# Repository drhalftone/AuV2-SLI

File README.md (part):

# AuV2-SLI — an FPGA structured-light scanner with the camera inside it

A **BYOP (Bring Your Own Projector) machine-vision camera**: an Alchitry **Pt V2**
(Xilinx Artix-7 **XC7A100T-2**) sits inline on HDMI between a PC and a projector, and carries
an **ON Semi PYTHON 1300** global-shutter sensor on a stacked daughter board. One bitstream
generates the structured-light patterns, drives the projector, triggers the sensor at a
commanded delay from the projected vsync, and streams 10-bit frames to the host over an
**Alchitry Ft+** (FT601Q) USB 3.0 link.

The FPGA can:

- **Pass HDMI through** from a PC to the projector, triggering the camera on each new frame.
- **Replace the video with on-board SLI fringes** — resolution-adaptive, generated on the fly.
- **Run fully offline, with no HDMI source at all** — it reads the projector's EDID and drives
  it at a mode the projector actually advertises, up to **1280×1024@60** or **800×600@120**.
- **Genlock capture to projection** — camera triggers are issued a programmable delay after the
  projected vsync, and **stack**, so patterns advance at the full HDMI frame rate instead of at
  (exposure + delay).
- **Stream to the PC over USB 3** — 1280×1024 × 10 bit, byte-exact, up to 120 fps sustained.

> The HDMI datapath is adapted from [hamsternz/Artix-7-HDMI-processing](https://github.com/hamsternz/Artix-7-HDMI-processing) (MIT).
> Original SLI design by Qishi Hu. This fork adds the EDID-driven offline output, the adaptive
> pass-through clocking, the CEA-aware EDID merge, the PYTHON 1300 receive chain, the Ft+ USB 3
> image path, and genlock.

---

## 0. Quick orientation — what this repo is, on one screen

| | |
|---|---|
| **FPGA** | Alchitry **Pt V2**, `xc7a100tfgg484-2` (the original Au V2 / XC7A35T build still exists — `build.tcl`) |
| **Top level** | `sources_1/imports/RTL/Au2_SLI.vhd` (VHDL, instantiating the Verilog subsystems) |
| **Current build** | `build_merged.tcl` → `build_merged/Au2_SLI_merged.{bit,bin}` — HDMI/SLI **+** camera **+** Ft+ |
| **Constraints** | `constrs_1/imports/RTL/Au2_pt.xdc` + `pt_ftplus_merged.xdc` |
| **Camera** | ON Semi **PYTHON 1300**, now the **colour** `NOIP1SE1300A` (Bayer) in an Andon socket — the mono `NOIP1SN1300A-QTI` before it. 1280×1024, global shutter, 4-lane LVDS @ 720 Mbps |
| **Camera board** | `LauPythonCamera_Pt_Stack/` — the KiCad board **and** its Verilog (`ddr/`) |
| **Image path** | Alchitry **Ft+** (FT601Q) USB 3.0 — ~325 MB/s measured, 132 fps at 10-bit |
| **Control path** | the same Ft+ (opcode-0 tunnel), **and** a 115200 UART on Port A (COM6) kept as an independent witness |
| **Frame buffer** | DDR3 via MIG — **mandatory**, the sensor reads out in a 4.55 ms burst at 576 MB/s |

**Two control links, on purpose.** Everything the host needs is reachable over the Ft+. Port A's
UART is kept because *the frame stream goes silent exactly when the camera fails* — the link that
can still answer in that state is the one worth having.

### Where to look

| Document | For |
|---|---|
| [`USB_COMMAND_REFERENCE.md`](USB_COMMAND_REFERENCE.md) | **Every get and put** — 11 writable registers, ~120 readable, 6 table targets, the Ft+ opcodes |
| [`FTPLUS_API.md`](FTPLUS_API.md) | The Ft+ control API, marked R / W / R-W |
| [`FRAME_HEADER_PLAN.md`](FRAME_HEADER_PLAN.md) | Per-frame header design (format 3 → 4): pairing, timestamps, `pat_period`. **§1a: the ROI mean now rides in word 1** |
| [`GENLOCK_MILESTONES.md`](GENLOCK_MILESTONES.md) | Locking exposure to the projected frame — G0…G3 |
| [`MERGE_MILESTONES.md`](MERGE_MILESTONES.md) | How HDMI and camera were merged onto one FPGA — M0…M7 |
| [`PT_PASSTHROUGH_DEBUG.md`](PT_PASSTHROUGH_DEBUG.md) | Pass-through bring-up on the Pt, and the bug that broke 640×480 for 16 months |
| [`CAMERA_RTL_PLAN.md`](CAMERA_RTL_PLAN.md) / [`CAMERA_RTL_REVIEW.md`](CAMERA_RTL_REVIEW.md) / [`CAMERA_SENSOR_PROTOCOL.md`](CAMERA_SENSOR_PROTOCOL.md) | The camera receive chain: plan, review, datasheet constants |
| [`PC_INTERFACE_INVENTORY.md`](PC_INTERFACE_INVENTORY.md) | Complete PC ↔ FPGA comms inventory |
| [`ROADMAP.md`](ROADMAP.md) / [`MIPI_CSI2_ROADMAP.md`](MIPI_CSI2_ROADMAP.md) / [`POLARFIRE_PORT_FEASIBILITY.md`](POLARFIRE_PORT_FEASIBILITY.md) | Board stack, a MIPI CSI-2 receiver, a PolarFire port |

---

## 1. RTL module map

Paths relative to `sources_1/imports/RTL/` unless noted.

### 1.1 Top level and clocking

| Module | Role |
|---|---|
| `Au2_SLI.vhd` | **Top.** Instantiates everything; owns mode selection, the DRP retune, `ext_sync`, the boot retune one-shot |
| `clk_selector.v` | Chooses between the recovered pass-through clock and the offline generated clock (`sel`) |
| `drp_clkgen13.v` | The **offline** output-clock MMCM — 13 curated modes, retuned over DRP |
| `drp_recfg.v` | DRP write sequencer for `drp_clkgen13` (per-mode M/D/O words) |
| `rx_drp_recfg.v` | DRP sequencer for the **recovery** MMCM (pass-through side) |
| `rx_freq_band.v` | Picks the recovery-MMCM band from the **measured** input frequency — this is what makes pass-through adaptive rather than fixed-×15 |

Clock domains: `clk100` (control / EDID / USB), the pixel clock and its ×5 (`pixel_io_clk_x5`),
`wordclk` (72 MHz, recovered from the sensor's LVDS), and MIG's `ui_clk`.

### 1.2 HDMI receive (pass-through)

| Module | Role |
|---|---|
| `hdmi_io.vhd` | Wrapper for the input and output halves of the HDMI stream |
| `hdmi_input.vhd` | Decoded-stream assembly: control periods, data islands, sync extraction |
| `input_channel.vhd` | One TMDS channel: deserialise → align → decode (Mike Field) |
| `deserialiser_1_to_10.vhd` | ISERDESE2 1:10 |
| `alignment_detect.vhd` | **Bitslip search.** `signal_quality` accumulates `x"100000"` per error and trips at bit 27 |
| `tmds_decoder.vhd` | 10b → 8b TMDS decode |
| `video_meas.v` | Measures the **incoming** timing: h/v active, frame period, validity (regs `0x60`–`0x6A`) |
| `video_phase_fifo.v` | Elastic phase-compensation buffer across the recovered-clock boundary |

> **`alignment_detect.vhd` is the one to remember.** A dropped hex digit (`x"000100"` instead of
> `x"100000"`, introduced 2025-04-17) made the bitslip search **4096× too slow** — 31 ms per tap
> instead of 7.6 µs. Fast pixel clocks still converged; **640×480 never did.** Restoring the
> upstream constant fixed 640×480@60 and @75 pass-through.

### 1.3 HDMI transmit

| Module | Role |
|---|---|
| `dvid_output.vhd` | DVI/HDMI output assembly (guard bands, preambles, control codes) |
| `tmds_encoder.vhd` | 8b → 10b TMDS encode |
| `serialiser_10_to_1.vhd` | OSERDESE2 10:1 — **the ceiling**: ×5 must stay under ~600 MHz |
| `video_timing_gen_rt.v` | **Runtime-configurable** timing generator for offline mode |
| `mode_timing_rom.v` | Per-mode video geometry lookup, keyed by `mode_idx` |
| `mode_table.vh` | The 14 curated modes (§4) |

### 1.4 EDID

| Module | Role |
|---|---|
| `i2c_master_edid.v` | Bit-banged I²C master; reads the **projector's** EDID off the output DDC |
| `edid_merge.v` | Self-contained merge unit + hot-plug ownership; re-probes every ~0.5 s |
| `edid_builder.v` | Builds the merged block served to the PC (monitor name `FPGA-PT`) |
| `edid_serve.vhd` | RAM-backed DDC **slave** on the input connector |
| `mode_select.v` | Parses the display EDID → supported-mode mask → the pick (regs `0x20`–`0x2A`) |

> `edid_fall` (reg `0x82`) counting **exactly 2/s is healthy** — it is the 0.5 s monitor-presence
> probe, not a fault. This was misdiagnosed twice.

### 1.5 Pattern generation

| Module | Role |
|---|---|
| `pattern_gen.v` | **Resolution-adaptive fringe DDS** (§5) |
| `pixel_pipe.v` | Pattern/pass-through mux, top-left-pixel trigger detection, the ready-paced GPIO handshake |
| `vga.vhd` | The offline test pattern — nested colour squares (`h`, `v`, `h xor v`) |

### 1.6 Camera — PYTHON 1300

RTL under `sources_1/imports/RTL/` and `LauPythonCamera_Pt_Stack/ddr/`.

| Module | Role |
|---|---|
| `cam_lvds_rx.v` | 1:10 LVDS receiver, PLL mode, per-lane IDELAYE2 |
| `cam_align.v` | Per-lane training / bitslip alignment |
| `cam_sync_decode.v` | Sync-channel decode + 4-lane de-interleave (proven bit-exact against the OVC reference) |
| `cam_spi_master.v` | 9-bit-addr / 16-bit-data SPI to the sensor |
| `cam_boot_seq.v` | ROM-driven power-up sequencer |
| `cam_cds_rom.v` | The CDS / sequencer **timing program** (104 writes, regs 384–474 and friends). `cam_boot_seq` uploads it after the boot ROM — **without it the pixel array does not work** (§10) |
| `cam_line_buf.v` | One-line capture buffer (bring-up) |
| `cam_async_fifo.v` | Dual-clock gray-pointer FIFO, **FWFT** |
| `cam_reply_fifo.v` | Control-plane reply bytes, `clk100` → `ui_clk` |
| `ddr/cam_frame_ft.v` | **The datapath.** Camera → DDR3 → FT601. Owns exposure, trigger period, re-arm, frame count, the genlock delay engine, and `cam_stat_o` |
| `ddr/cam_expo_safety.v` | **Makes a sensor wedge impossible** — clamps every exposure command, shortens the exposure when the rate rises, holds the trigger while a longer exposure may still be in effect (§7.4). Gate: `sim/tb_expo_safety.v` |
| `ddr/cam_frame_ddr.v`, `ddr/ddr_bist.v`, `ddr/ddr_loop_ft.v`, `ddr/ft_probe_bottom.v` | Bring-up harnesses, kept as isolation tests |

> **The DDR3 is not optional.** The sensor reads a frame out in a **4.55 ms burst at 576 MB/s**
> against a 325 MB/s link. Live video cannot bypass the buffer, and lowering the frame rate does
> not help — the *burst* rate is what exceeds the link.

> `cam_async_fifo`'s `ram_style="block"` is **ineffective** (combinational FWFT read): 0 BRAMs are
> used. FIFO depth is not an available remedy.

### 1.7 Host link

| Module | Role |
|---|---|
| `uart_rx.v` / `uart_tx.v` | 8N1, LSB first |
| `uart_ctrl.v` | The `0xA5` control protocol — register file, table upload/readback |
| `status_line.v` | The one-line telemetry stream |
| `usb_link.v` | Arbitrates telemetry vs. command replies; **derives the max usable exposure** (§7.4) |
| `led_idle_anim.v` | "Sign of life" idle animation over the status LEDs |

---

## 2. Operating modes

### 2.1 Pass-through with top-left-pixel (TLP) trigger
The PC plays the patterns; the FPGA forwards the video unchanged, samples the **top-left pixel** of
each frame, and fires a camera pulse on the next VSYNC when that value changes.

### 2.2 Pass-through with on-board SLI patterns
The FPGA **replaces** the incoming frames with locally generated fringes. Orientation (`SW[0]`),
per-channel enables (`SW[3:1]`) and the frame/frequency sequencing drive it at runtime; all four
switches are overridable over USB (`SLICTRL`, reg `0x13`).

### 2.3 Offline (EDID-driven) — no HDMI source required
With nothing on the input, the FPGA generates everything from its own 100 MHz oscillator. The
output pixel clock **and** the video timing are reconfigured at runtime to match the projector's
EDID: a dedicated `MMCME2_ADV` is retuned over DRP and `video_timing_gen_rt` is loaded from the
curated table.

> **Boot retune one-shot.** On power-up the DRP retune pulse used to be issued before the MMCM had
> locked, and was discarded — a blank screen on every cold boot. `Au2_SLI.vhd` now re-issues
> `clkgen_sen` once at **1 s** after configuration (`boot_cnt = 100_000_000` on `clk100`).
> `boot_cnt` is declared `integer` deliberately: both `STD_LOGIC_ARITH` and `NUMERIC_STD` are in
> scope in that file, so an `unsigned` would be ambiguous.

---

## 3. Genlock — the reason the FPGA is inline

`ext_sync` is the **output** vsync (`Au2_SLI.vhd`: `ext_sync => out_vsync`) delivered into
`cam_frame_ft.v`. Camera triggers are issued a programmable delay after it.

**Triggers stack.** Because the delay and the exposure are both known exactly, the delay engine is a
*fire-time queue*, not a wait-for-ready handshake:

```verilog
localparam [23:0] XS_TIMEOUT = 24'd10_000_000;   // 100 ms with no vsync -> fall back
localparam integer GLQ_AW    = 5;                // 32 outstanding triggers
reg [23:0] gl_now;                               // free-running 10 ns time base
reg [23:0] glq [0:31];                           // absolute fire-times
wire [23:0] gl_late = gl_now - glq[glq_rd];      // top bit CLEAR = deadline passed
wire gl_push = xs_rise && gl_live && !glq_full;
wire gl_pop  = !glq_empty && !gl_late[23];
```

So with a delay longer than a frame, **patterns advance at the full HDMI rate** — the capture of
pattern *k* simply arrives while pattern *k + floor(D/T)* is on screen. That pairing offset is
`floor(D/T)`; read it from reg `0x5E` (outstanding). **Do not assume it** — an offset wrong by one
yields a phase map that looks plausible and is wrong everywhere.

- `gl_en` is what was **commanded**; `gl_live` is whether `ext_sync` is actually arriving. They
  differ exactly when the display has gone away and the trigger has fallen back to free-running.
- Set it over the Ft+: **opcode 7**, `{4'd7, gl_en, 3'b0, delay[23:0]}`, delay in 10 ns ticks.
- Read it back over the UART: `0x5A`–`0x5C` delay, `0x5D` `{gl_live, gl_en}`, `0x5E` outstanding,
  `0x5F` FIFO overflows.

> **Sync must be held across the whole control period.** `hdmi_input.vhd` used to clear
> `raw_vsync`/`raw_hsync` alongside `raw_blank`, so on the 8 of 14 modes with **negative** vsync
> polarity `ext_sync` fired once per *line*. Sync is now assigned only from `ch0_ctl`.

**Now proven, photometrically** — see 3.1. Nothing on the board sees photons, so this was measured
by sweeping the genlock delay across a whole frame and reading the camera's own ROI mean.

### 3.1 Where the light actually is — measured on an Optoma ML750ST

Swept with `host/sli_frame_sweep.py`: white SLI fringes (finest octet) cycling one per frame, the
genlock delay walked across the entire frame period in **1 µs steps, 8326 points**, ROI mean at each.
Projector at **120 Hz**, which on this model forces **3D mode**. Frame period 8325.8 µs.

| | µs |
|---|---|
| first light | **573** |
| last light | **6682** |
| span | **6109** |
| floor / peak | 191 / 890 ADU |

**Use these settings to scan:**

| | value |
|---|---|
| genlock delay | **540 µs** (`0x5A`–`0x5C`, 10 ns ticks → 54000) |
| exposure | **6175 µs** → **16467** units of 375 ns (`0x1A`/`0x1B`) |

That window is `573 − 33` to `6682 + 33`. The 33 µs is not timing jitter: the sensor's effective
exposure floor is somewhere between 20 and 400 µs, so the measured edges are smeared by the sampling
aperture and the true transitions can sit ~30 µs either side. The window closes at 6715 µs, leaving
**1611 µs clear** before the next frame, so widening the margin is free.

What the sweep shows, and why each part matters:

- **The edges are sharp.** Moving the detection threshold from 5 % to 20 % of full scale shifts the
  onset 573 → 576 and the offset 6682 → 6678. These are hard transitions, not ramps, so the delay
  does not need trimming by eye.
- **Five dark gaps sit inside the window** — 284, 153, 151, 160 and 285 µs. A single exposure has to
  span all of them; there is no shorter window that catches the light.
- **A weak shoulder runs 112–573 µs**, peaking 32 ADU over the floor. It is **0.59 % of the frame's
  light** and not worth 460 µs of exposure. Everything outside 573–6682 together is under 1.2 %.
- **Between bursts the signal returns to ~210 ADU over a 191 floor.** Under a *solid* white field the
  same projector never drops below 722 anywhere in the frame. The high "background" in solid-field
  measurements belongs to the content on the screen, not to LEDs that cannot switch off — which is
  why this measurement had to be made with fringes up, not with a flat field.

**Probably true of other Optoma DLP projectors, but do not assume it.** The structure here — bit-plane
PWM in flat-topped rectangles, field-sequential RGB, sub-field groups separated by ~150–285 µs — comes
from the DisplayLink/DLP controller family rather than from this chassis, so the shape should carry
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
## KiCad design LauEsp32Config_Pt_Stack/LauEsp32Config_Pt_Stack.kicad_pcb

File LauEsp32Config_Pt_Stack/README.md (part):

# ESP32 wireless programmer — Pt V2 element card

_Started 2026-09-02. Nothing is built. Scope is deliberately narrow: **reprogram
the Pt V2's FPGA over WiFi from a board inside the stack.** Everything needed
electrically is now confirmed from Alchitry's own Rev A schematic and pinout sheet,
both in `docs/`. Read the **rev B warning** in §3 before committing a layout._

---

## 1. Why this board exists

**The Ft+ cannot configure the FPGA, and it is the only host↔FPGA link this camera
has.** That single fact is the whole justification.

Today the Pt is programmed over its own USB-C through the FT2232H, by the Alchitry
loader. Fine on a bench with the enclosure open; not fine for

- a camera **sealed in the printed enclosure**, where the Pt's USB-C is not meant
  to be user-accessible;
- a **just-in-time workflow** — write HDL, compile, push — where walking a cable to
  the part defeats the point;
- **multiple cameras**, where the cable count grows with the array.

So: an element card carrying an ESP32, sitting in the stack, driving the FPGA's
JTAG from inside. It replaces the GPIO board currently used as a spacer, so it
costs no stack height that is not already accounted for.

> The founder of Alchitry, who designed these boards, says the approach should
> work. §3 and §4 are the pin- and part-level confirmation of that.

## 1a. Stack position — in place of the Sp spacer between Ft+ and Hd. VERIFIED 2026-09-16

```
   [ camera element ]      top of the Pt
     Alchitry Pt V2
   [ Sp ]                  clears the Pt's bottom-side caps
   [ Ft+ ]
   [ ESP32 card ]          <- replaces the second Sp (micro-HDMI / USB cable clearance)
   [ Hd ]
```

Checked against Alchitry's own schematics (`docs/Alchitry_Platinum_RevA_schematic.pdf`
sheet 4, `docs/FtPlusSchematic.pdf`, `docs/HdSchematic.pdf`), read from rendered images:

- **Connector genders match.** Pt, Ft+ and Hd all carry `DF40C-xxDS-0.4V(4.0)` receptacles on
  top and `DF40C-xxDP-0.4V` plugs on the bottom. This card does the same, so it fits
  anywhere a spacer fits.
- **The control signals reach this slot.** The Ft+ and the Hd pass control pins C29–C50
  straight through and use none of them.
- **Alchitry numbers every bottom plug mirrored.** On all three boards, bottom plug pin *2k*
  mates receptacle pin *2k−1*: the Pt's J8 has +3V3 on **even** 1–16, RESET on 38, TCK on 50.
  Carried through the Ft+ into this card's top receptacle (receptacle numbering), the pins
  land **exactly where §3 and the schematic assume**: +3V3 odd 1–15, 37 Reset, 39 DONE,
  41 PROGRAM_B, 43 TDI, 45 TDO, 47 TMS, 49 TCK. **No netlist change is needed.**
- **The FPGA nets on 29–36 are NOT the ones in §3b.** §3b decoded the Pt's *top* connector.
  Below the Pt they come from J8, the bottom connector:

  | Card pin | FPGA net (Pt J8) | | Card pin | FPGA net (Pt J8) |
  |---|---|---|---|---|
  | 29 `FAB_SCK` | `34_L1_N` | | 30 `FAB_IO2` | `34_L15_N` |
  | 31 `FAB_MOSI` | `34_L1_P` | | 32 `FAB_IO3` | `34_L15_P` |
  | 33 `FAB_IRQ` | `34_L3_N` | | 34 `FAB_MISO` | `34_L6_N` |
  | 35 `FAB_SPARE` | `34_L3_P` | | 36 `FAB_CS` | `34_L6_P` |

  All are bank 34, hardwired 3.3 V, and they are still true N/P pairs. Constrain them **by
  package pin** from Alchitry's `pt_*_bottom` constraint files (bank-16/34 labels are swapped
  in the schematic, §3b).

**Mechanical consequences:**
- **Stack height is unchanged.** The gap on each side stays 4.125 mm (§6.3).
- **Top face:** faces the Ft+ underside, which has no components (§6.3). The whole gap is usable.
- **Bottom face:** now faces the **Hd's top side, where its micro-HDMI receptacles are.**
  Cable clearance there is what the spacer was for. **Measured from the Hd STEP (§6.3):**
  ≥ 2.67 mm under the card everywhere except over the two HDMI connectors (1.15 mm). That area
  is now a B.Cu no-footprint rule area (x 0–9.5, y 17.5–40, left edge).
- **Rev B:** Alchitry's "JTAG pins will change places" note is on the *top* connector
  column of the rev A pinout sheet. Whether the bottom connector changes too is unconfirmed.
  The straps (`SCHEMATIC.md` §4) cover the published Au order either way.

## 2. Configure RAM, never the boot flash

**The bitstream goes into the FPGA's volatile configuration memory. The QSPI boot
flash is never written.**

The consequence is the point: **power-cycling the camera restores its camera
functionality.** The Pt reloads the shipped image from flash on boot, so whatever
experimental bitstream was pushed is simply gone.

That makes the failure mode of a bad JIT build *a reboot*, not a brick. A pipeline
that can write boot flash can permanently kill a sealed unit; one that can only
write configuration RAM cannot. **Treat "never touch the QSPI flash" as a design
rule, not a phase-one simplification.**

The schematic reinforces it: **`CCLK_0` (L12) is shared with `QSPI_SCK`** — the
configuration clock and the flash clock are the same net. Anything driving
configuration is already adjacent to the flash bus, so the separation has to be
kept deliberately, in firmware.

## 3. J3 "Control" — the connector this board lives on

From Alchitry's **"Pinout and Trace Lengths"** sheet, exported to
`docs/Pt_V2_pinout_trace_lengths.csv`. Generated from the CSV, not transcribed.
**Identical on the top and bottom sides**, so a pass-through card sees the same map
on both faces.

| Pin | Signal | | Pin | Signal |
|---|---|---|---|---|
| 1–15 odd | `+3V3` | | 2–16 even | `RAW` |
| 17–27 odd | `GND` | | 18–28 even | `GND` |
| 29, 33 | `IO_N` | | 30, 34 | `IO_N` |
| 31, 35 | `IO_P` | | 32, 36 | `IO_P` |
| **37** | **`Reset`** | | 38 | `VBSEL_A` |
| **39** | **`DONE`** | | 40 | `VBSEL_B` |
| **41** | **`Program`** | | 42 | `A1V8` |
| **43** | **`TDI`** | | 44 | `AVP` |
| **45** | **`TDO`** | | 46 | `AVN` |
| **47** | **`TMS`** | | 48 | `AREF` |
| **49** | **`TCK`** | | 50 | `AGND` |

Everything the board needs is here, and more than just the four JTAG pins:

- **`Program` (41)** — force a reconfigure rather than relying on JTAG state alone.
- **`DONE` (39)** — read back whether a push actually took. Without it the ESP32
  cannot tell the host a configuration succeeded, and a JIT loop would be debugging
  HDL when the load silently failed.
- **`Reset` (37)** — a clean way back to a known state.
- **`+3V3` on eight pins, `RAW` on eight** — take either rail.
- **Four spare `IO_N`/`IO_P` pairs (29–36)** — a side channel between ESP32 and
  fabric that costs nothing from Bank A or Bank B.

**`INIT_B` is NOT on J3.** It exists on the FPGA (U12) but does not reach the
connector, so the init/clear phase cannot be observed. `DONE` is the completion
signal available, and the firmware should not assume more.

> ### ⚠ THE JTAG PINS MOVE IN REV B
>
> Alchitry's sheet carries this note verbatim in the Control column:
>
> **"Note: JTAG pins will change places to match Au with rev B"**
>
> The table above is **rev A**. A layout hard-wired to these numbers is wrong on
> rev B, and the failure is not obvious — TDI/TDO swapped is a chain that does not
> respond, which reads exactly like a dead ESP32 or a bad joint. This project has
> already lost days to that class of fault twice: the LVDS eye that looked like bad
> solder, and the chip-ID silence that was three hand-solder defects.
>
> **Confirm the board revision before committing a layout**, and prefer a footprint
> that can be strapped, or a buffer whose pin order can be jumpered, over one that
> hard-wires rev A.

## 3b. A second path: SPI to the running design

J3 carries **four spare FPGA I/O pairs — eight signals — and the current designs use
none of them.** Decoded from sheet 3 of the Rev A schematic (Altium doubles
characters in the PDF text layer; these are the de-doubled net names):

| J3 pin | FPGA net | | J3 pin | FPGA net |
|---|---|---|---|---|
| 29 | `BANK14_L18_N` | | 30 | `BANK34_L5_N` |
| 31 | `BANK14_L18_P` | | 32 | `BANK34_L5_P` |
| 33 | `BANK34_L2_N` | | 34 | `BANK14_L23_N` |
| 35 | `BANK34_L2_P` | | 36 | `BANK14_L23_P` |

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
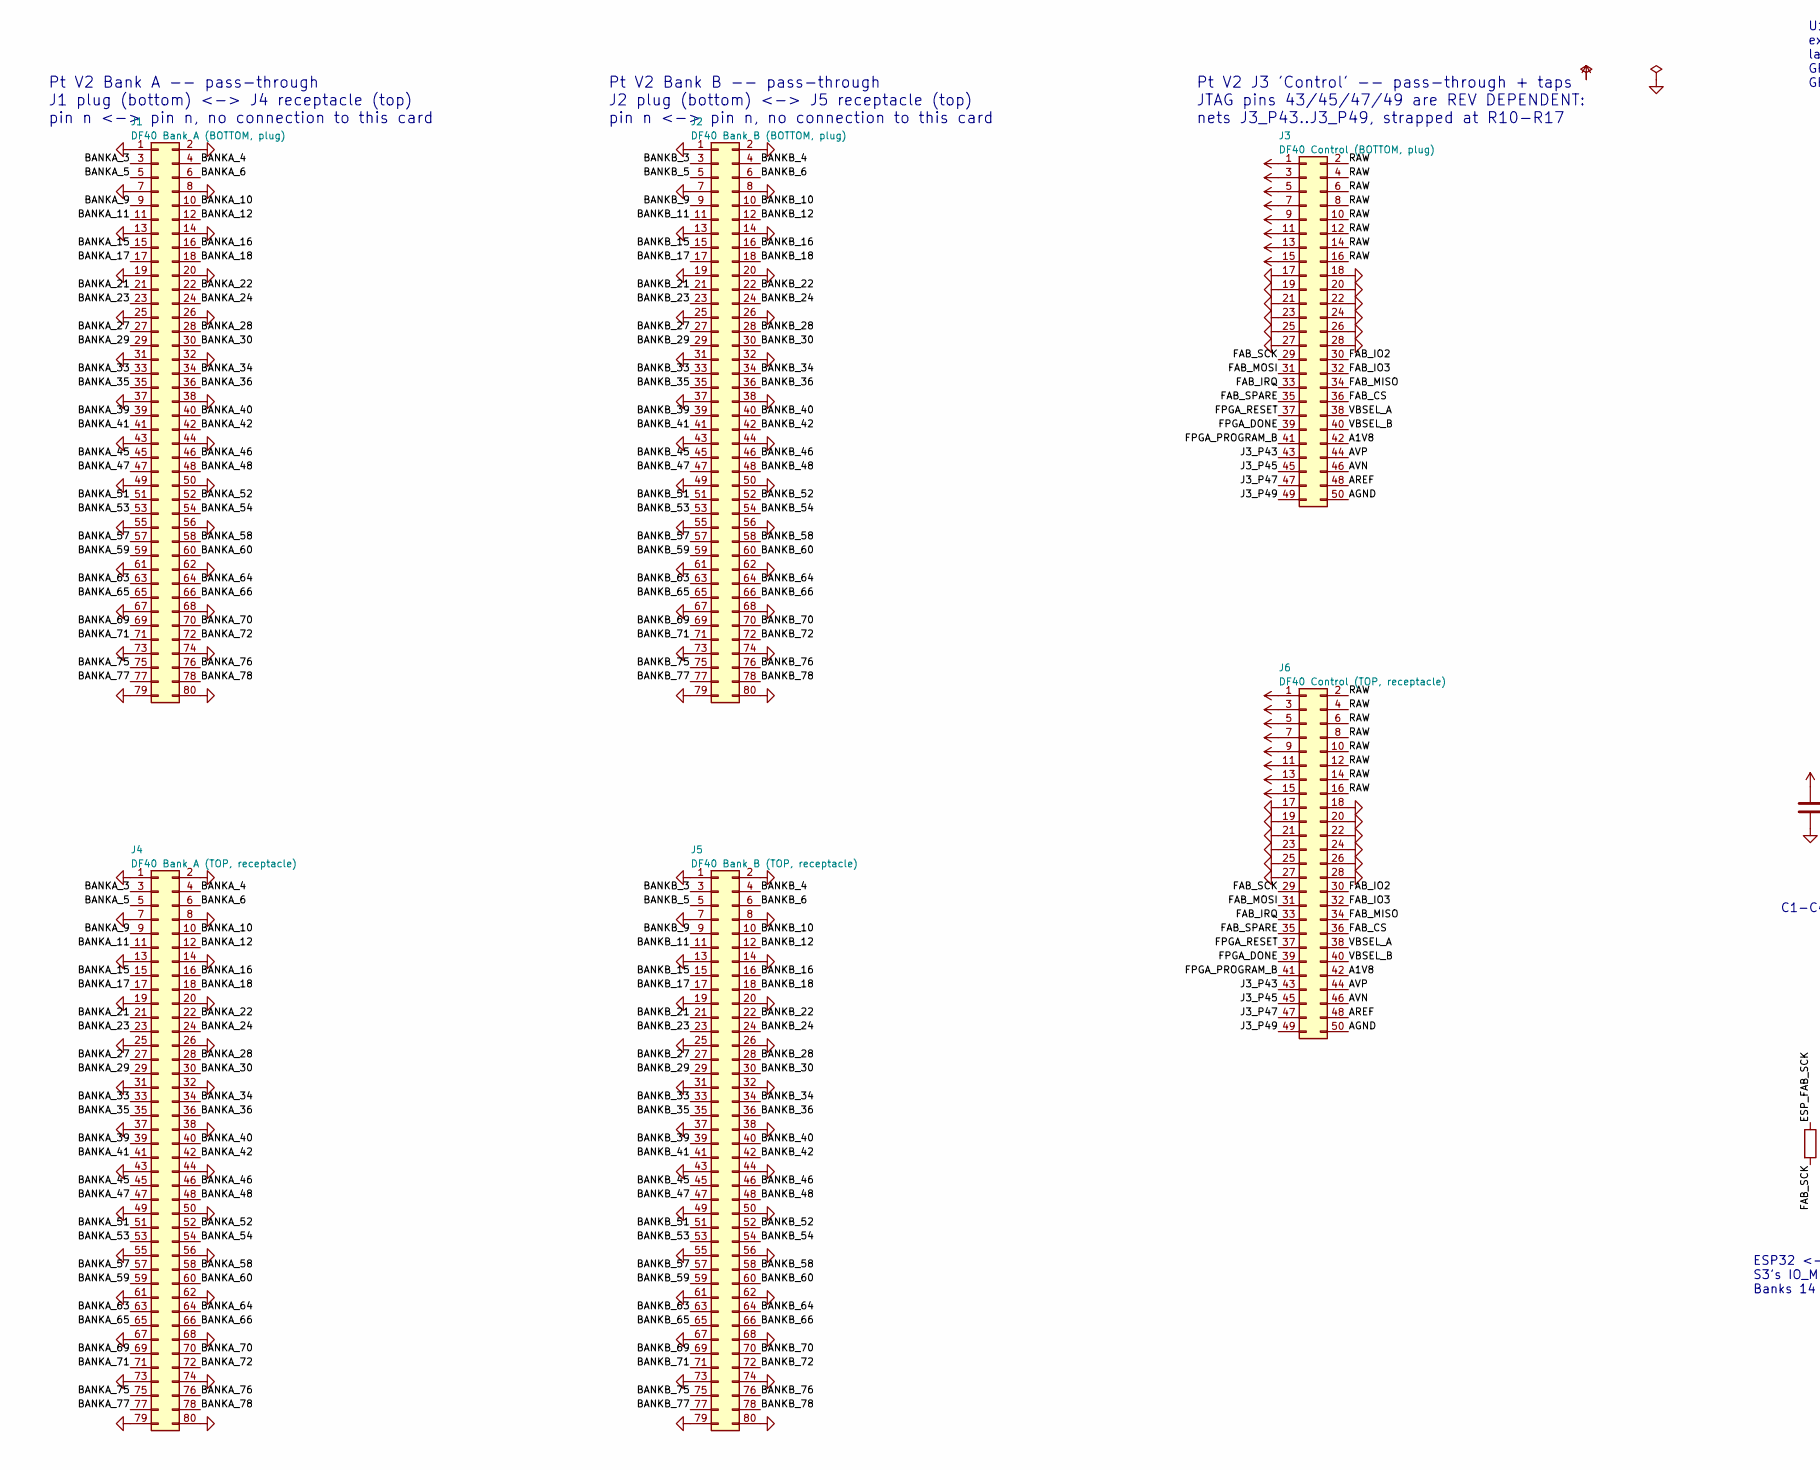
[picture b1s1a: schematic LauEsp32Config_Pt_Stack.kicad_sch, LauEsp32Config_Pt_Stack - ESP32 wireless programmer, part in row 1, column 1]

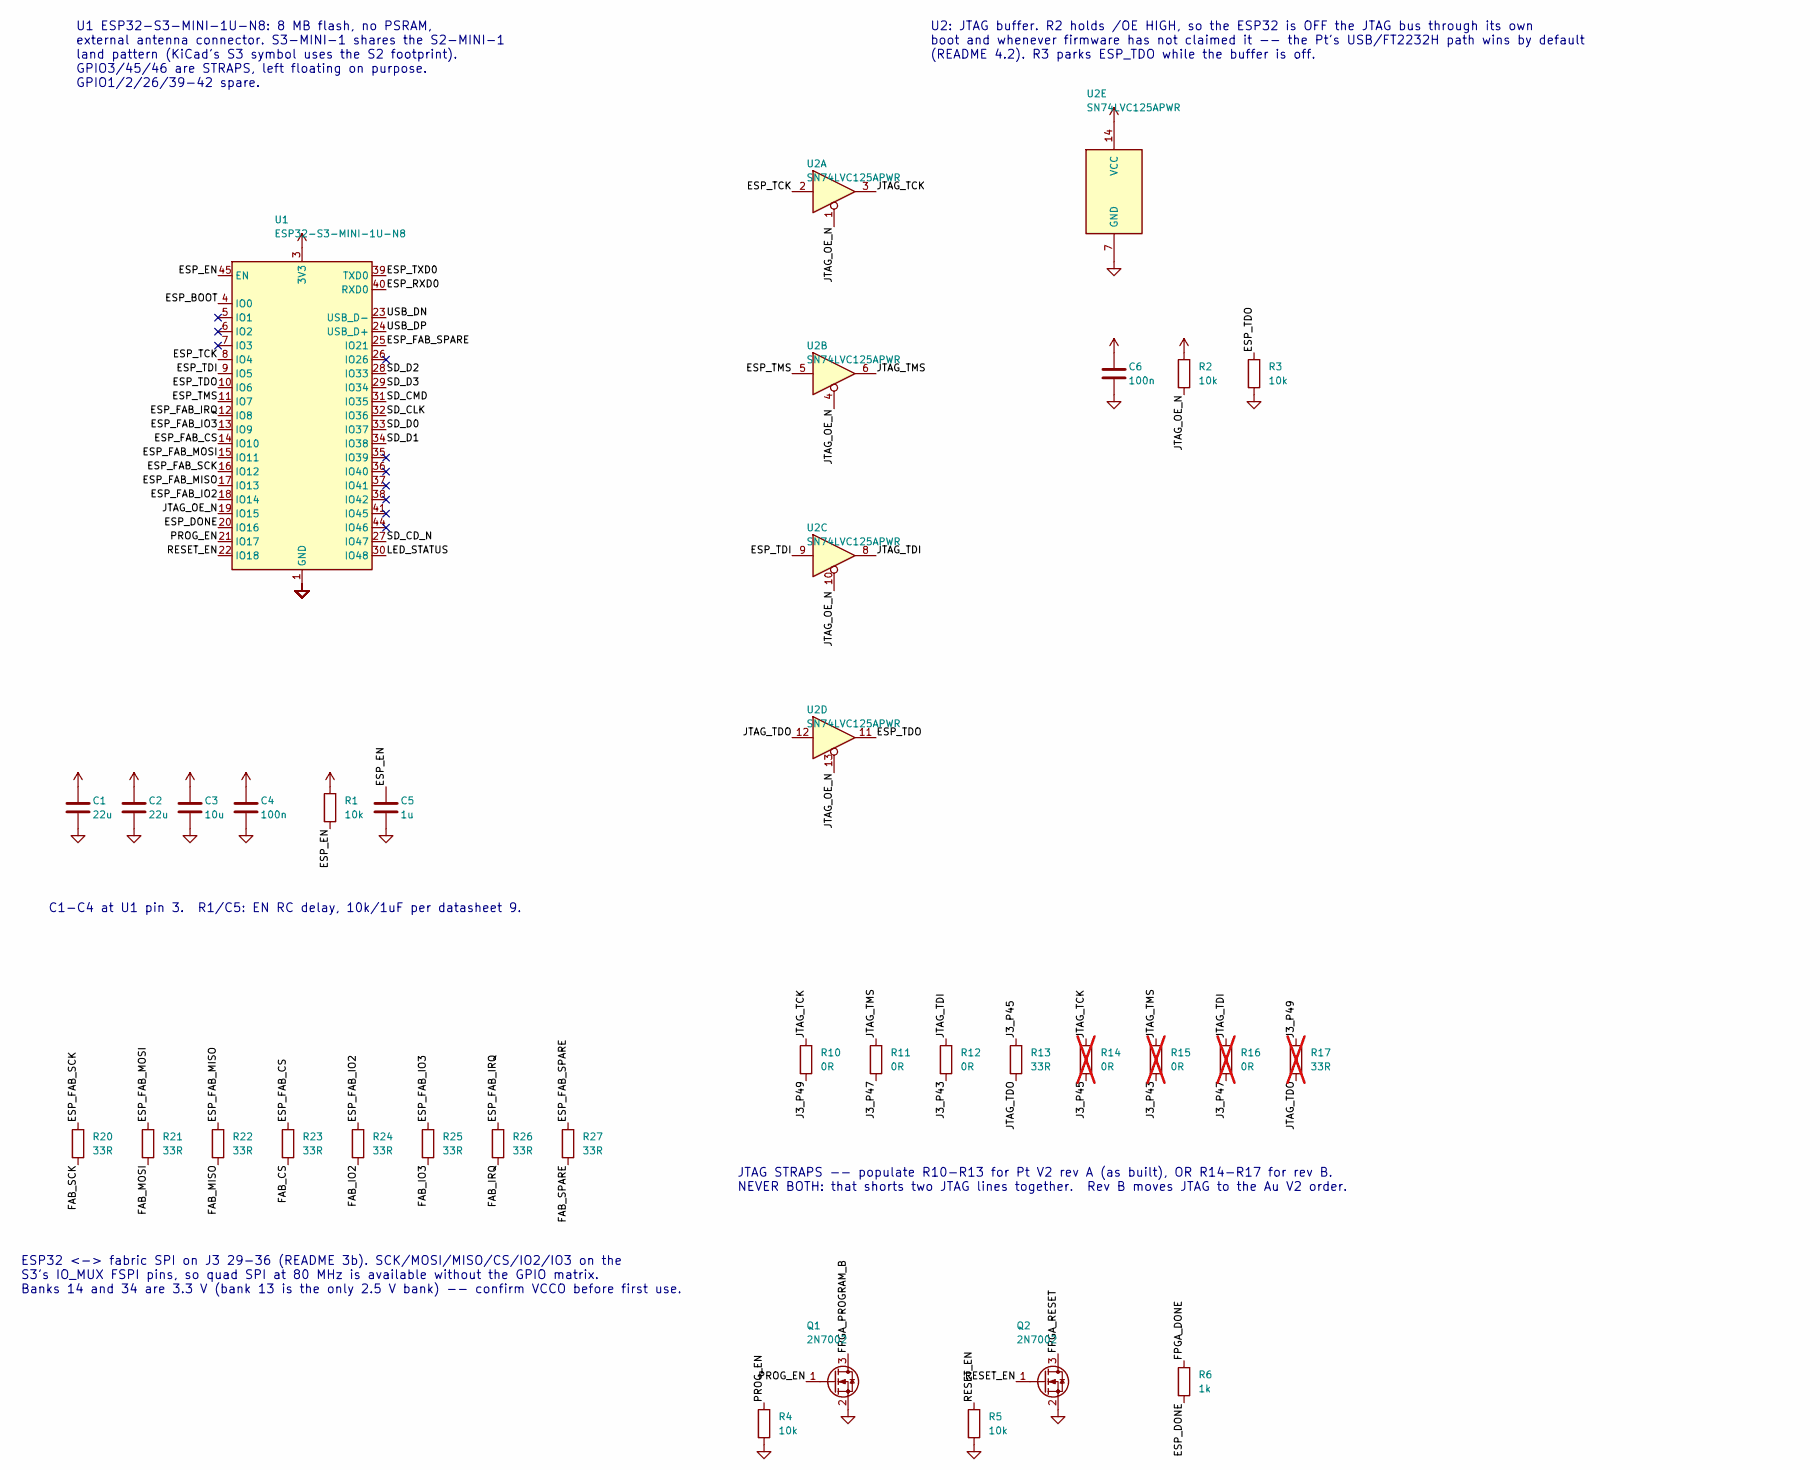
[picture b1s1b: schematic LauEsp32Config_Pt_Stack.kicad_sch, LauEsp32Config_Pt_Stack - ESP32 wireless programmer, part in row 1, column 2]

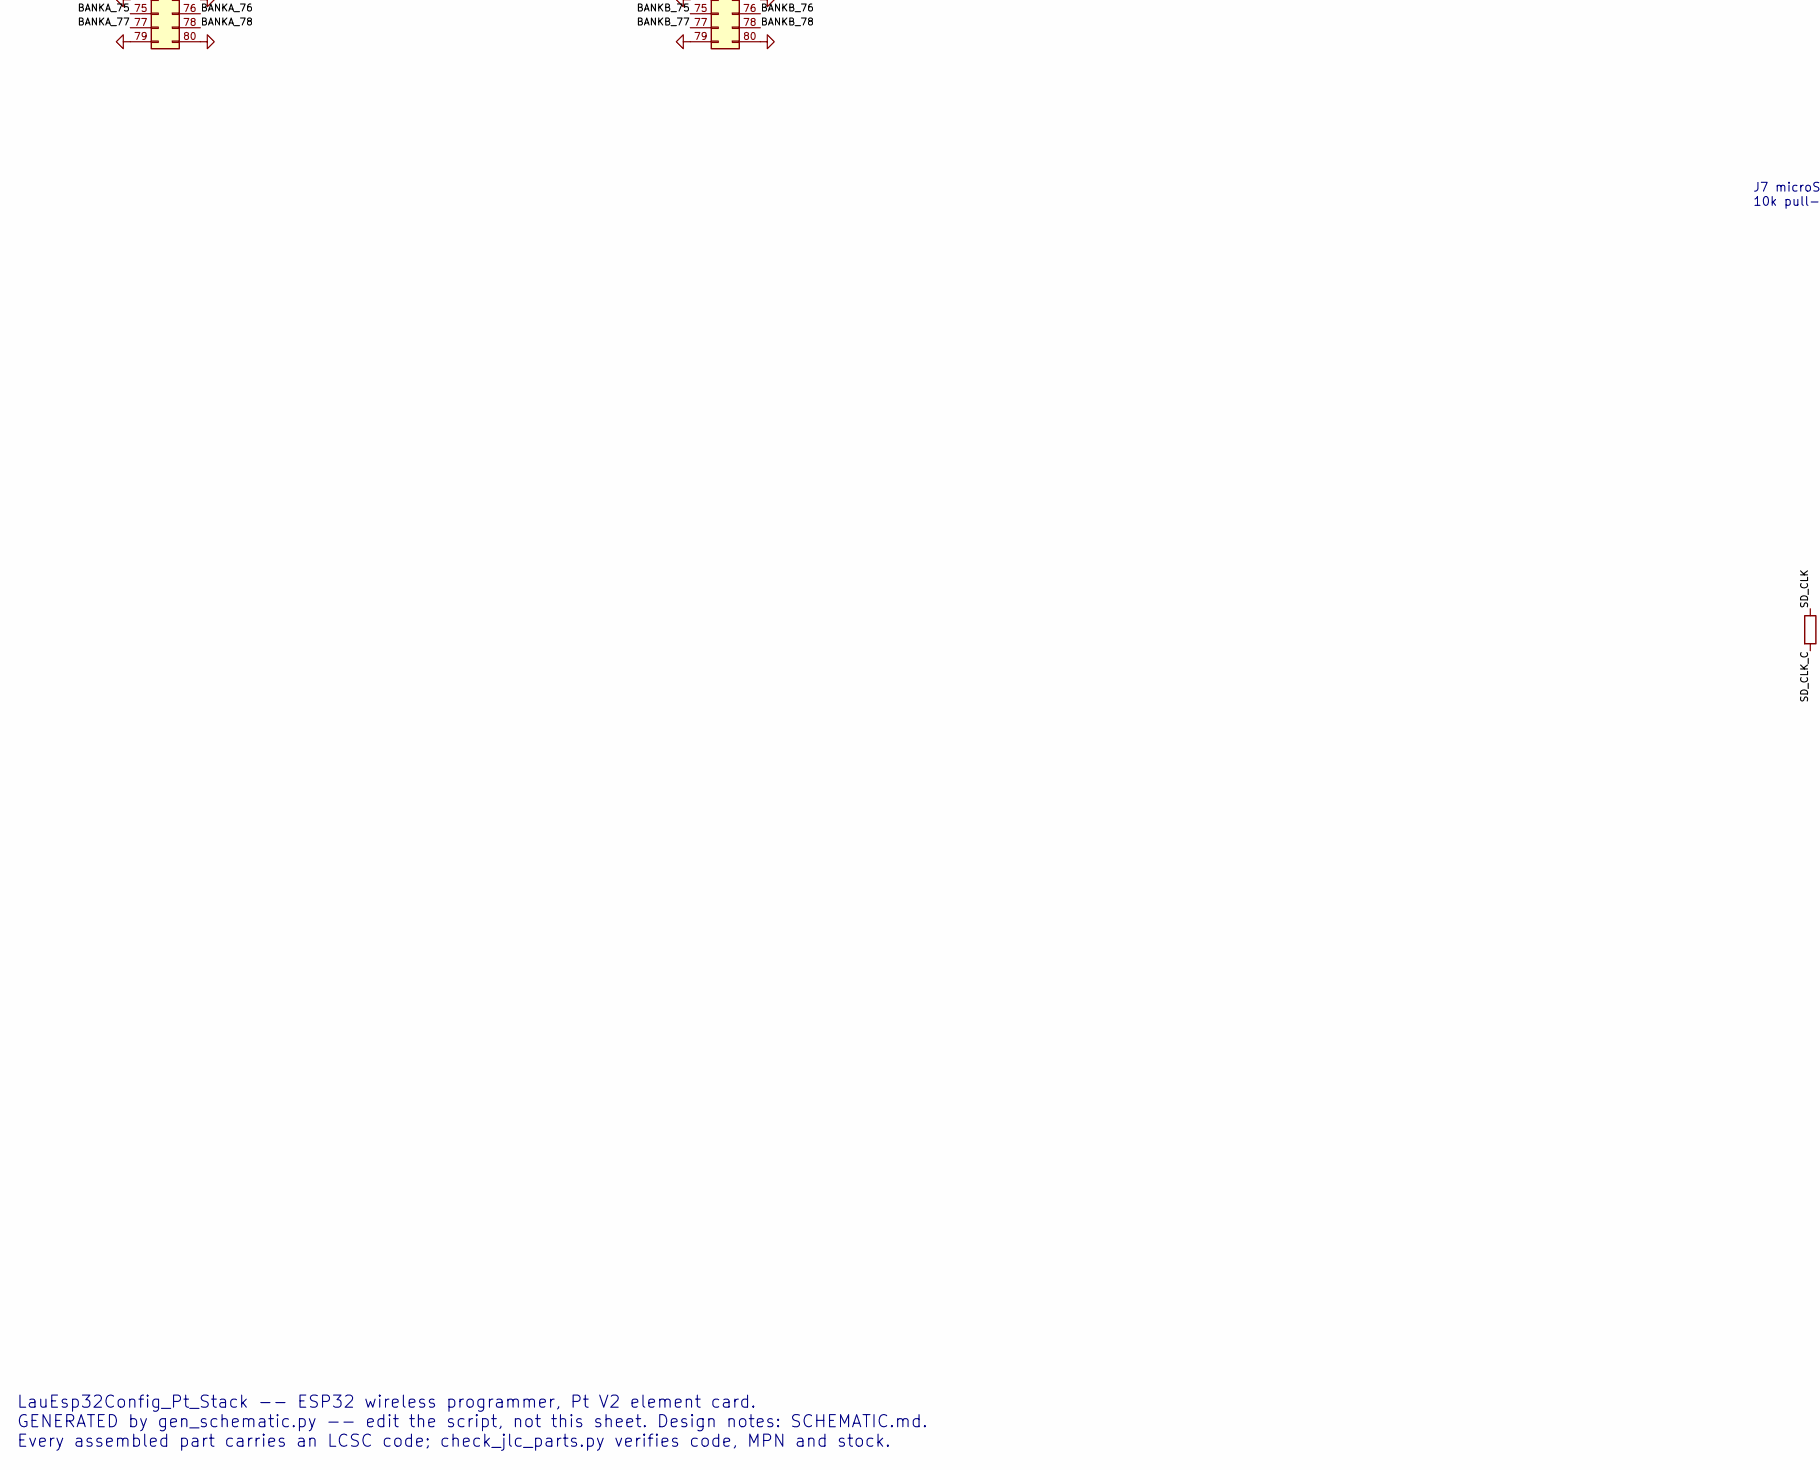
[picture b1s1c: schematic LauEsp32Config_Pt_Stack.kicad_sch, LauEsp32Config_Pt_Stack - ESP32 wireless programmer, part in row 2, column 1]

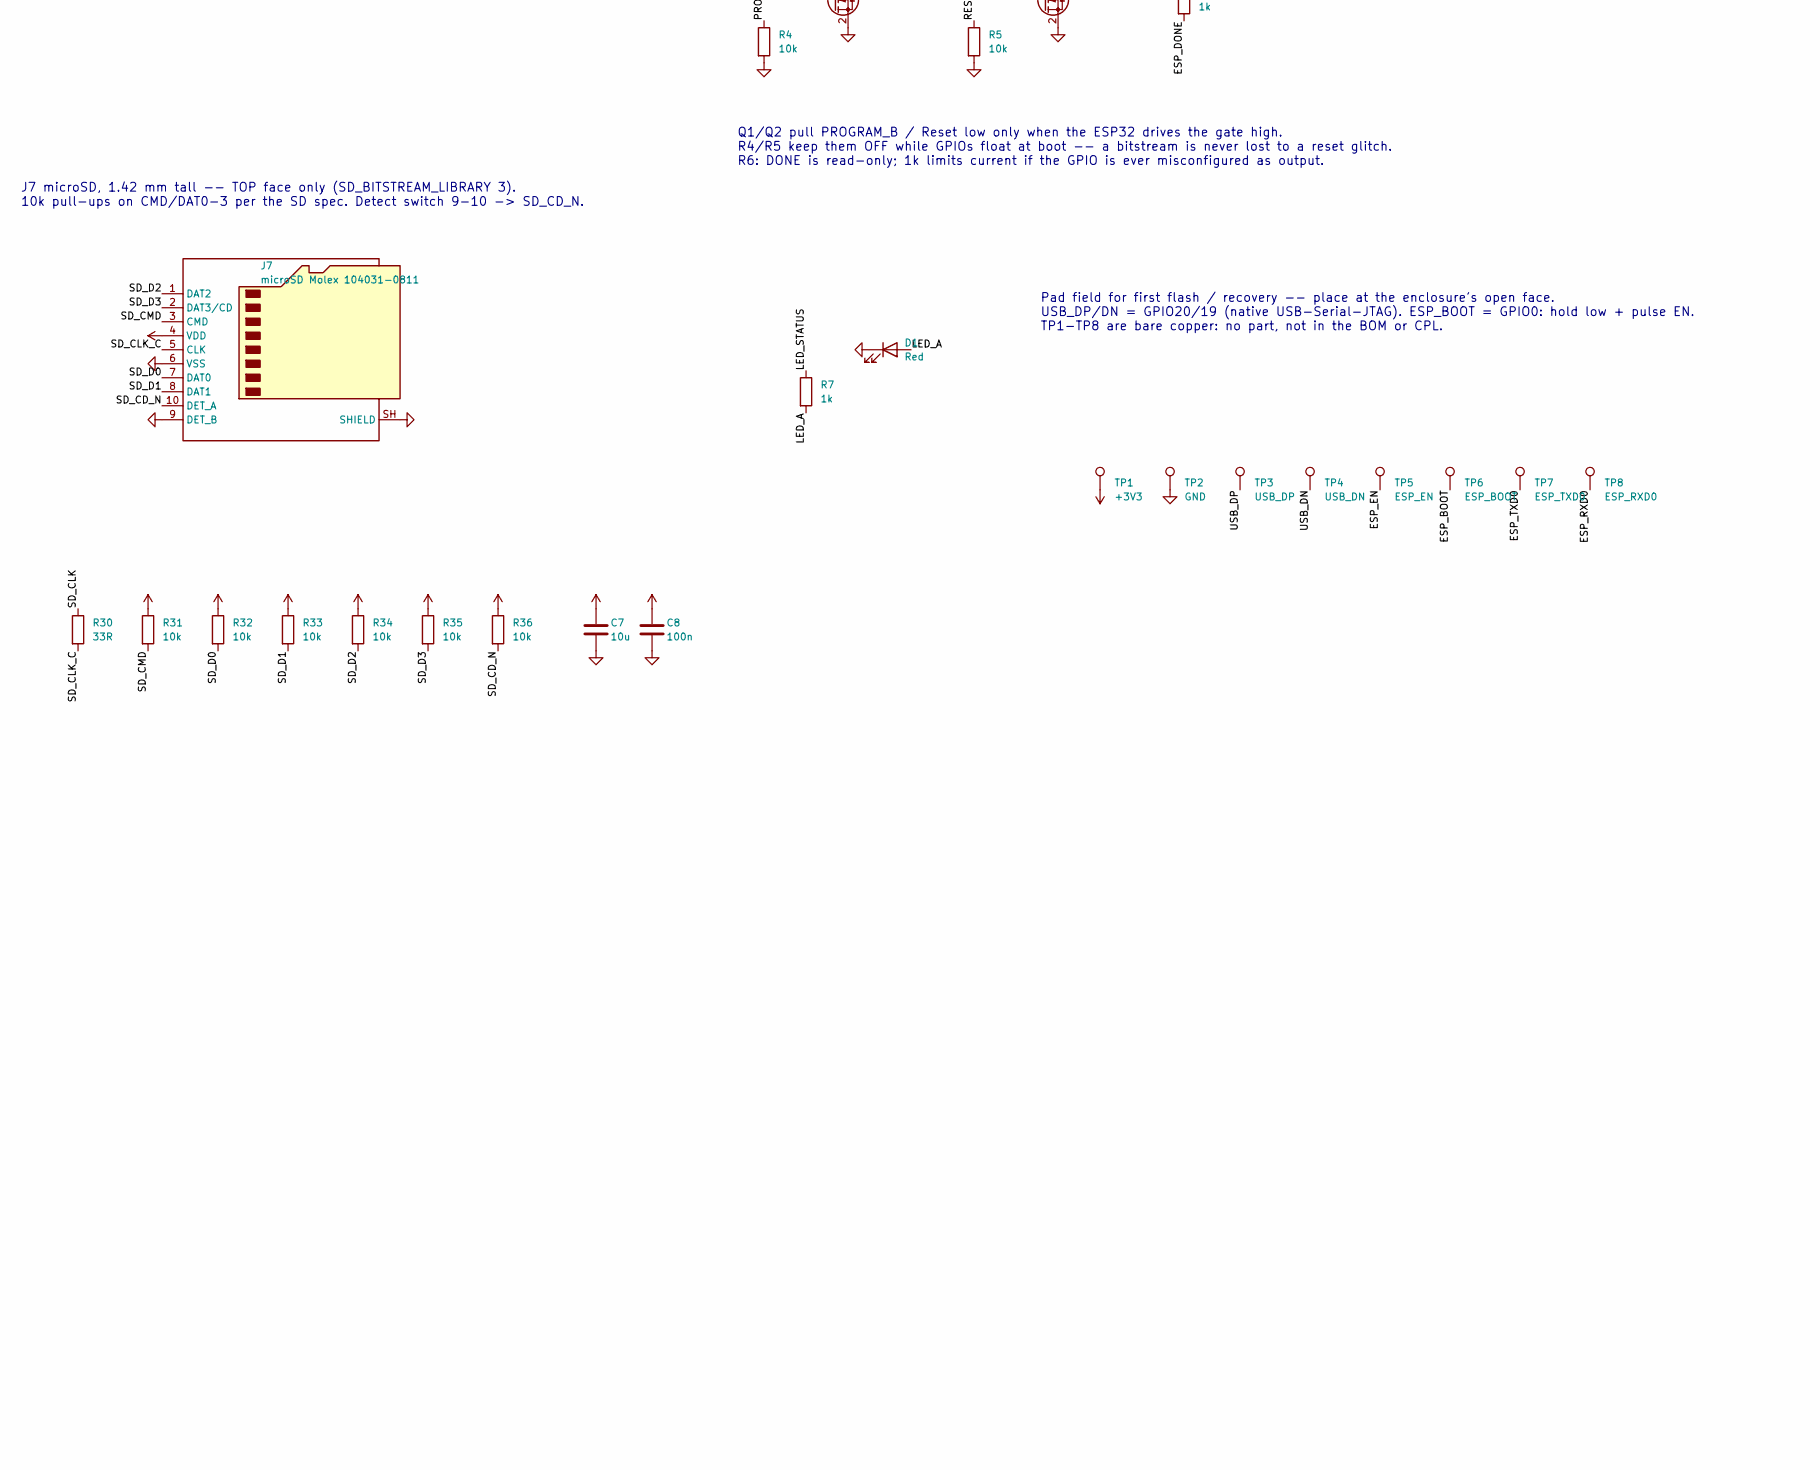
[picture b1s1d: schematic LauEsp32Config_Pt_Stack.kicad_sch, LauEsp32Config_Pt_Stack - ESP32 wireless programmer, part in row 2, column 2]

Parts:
C1, C2: 22u; C_0805_2012Metric; MPN CL21A226MAQNNNE; LCSC C45783
C3, C7: 10u; C_0805_2012Metric; MPN CL21A106KAYNNNE; LCSC C15850
C4, C6, C8: 100n; C_0402_1005Metric; MPN CL05B104KO5NNNC; LCSC C1525
C5: 1u; C_0402_1005Metric; MPN CL05A105KA5NQNC; LCSC C52923
D1: Red; LED_0603_1608Metric; MPN KT-0603R; LCSC C2286
J1: DF40 Bank A (BOTTOM, plug); Hirose_DF40C-80DP-0.4V_2x40-1MP_P0.4mm; MPN DF40C-80DP-0.4V(51); LCSC C294544
J2: DF40 Bank B (BOTTOM, plug); Hirose_DF40C-80DP-0.4V_2x40-1MP_P0.4mm; MPN DF40C-80DP-0.4V(51); LCSC C294544
J3: DF40 Control (BOTTOM, plug); Hirose_DF40C-50DP-0.4V_2x25-1MP_P0.4mm; MPN DF40C-50DP-0.4V(51); LCSC C424645
J4: DF40 Bank A (TOP, receptacle); Hirose_DF40HC(4.0)-80DS-0.4V_2x40_P0.4mm; MPN DF40HC(4.0)-80DS-0.4V(51); LCSC C5254351
J5: DF40 Bank B (TOP, receptacle); Hirose_DF40HC(4.0)-80DS-0.4V_2x40_P0.4mm; MPN DF40HC(4.0)-80DS-0.4V(51); LCSC C5254351
J6: DF40 Control (TOP, receptacle); Hirose_DF40HC(4.0)-50DS-0.4V_2x25_P0.4mm; MPN DF40HC(4.0)-50DS-0.4V(51); LCSC C5338326
J7: microSD Molex 104031-0811; microSD_HC_Molex_104031-0811; MPN 1040310811; LCSC C585350
Q1, Q2: 2N7002; SOT-23; MPN 2N7002; LCSC C8545
R1, R2, R3, R4, R5, R31, R32, R33, R34, R35, R36: 10k; R_0402_1005Metric; MPN 0402WGF1002TCE; LCSC C25744
R6, R7: 1k; R_0402_1005Metric; MPN 0402WGF1001TCE; LCSC C11702
R10, R11, R12: 0R; R_0402_1005Metric; MPN 0402WGF0000TCE; LCSC C17168
R13, R20, R21, R22, R23, R24, R25, R26, R27, R30: 33R; R_0402_1005Metric; MPN 0402WGF330JTCE; LCSC C25105
R14, R15, R16: 0R; R_0402_1005Metric; MPN 0402WGF0000TCE; LCSC C17168; not fitted
R17: 33R; R_0402_1005Metric; MPN 0402WGF330JTCE; LCSC C25105; not fitted
TP1: +3V3; TestPoint_Pad_D1.0mm
TP2: GND; TestPoint_Pad_D1.0mm
TP3: USB_DP; TestPoint_Pad_D1.0mm
TP4: USB_DN; TestPoint_Pad_D1.0mm
TP5: ESP_EN; TestPoint_Pad_D1.0mm
TP6: ESP_BOOT; TestPoint_Pad_D1.0mm
TP7: ESP_TXD0; TestPoint_Pad_D1.0mm
TP8: ESP_RXD0; TestPoint_Pad_D1.0mm
U1: ESP32-S3-MINI-1U-N8; ESP32-S2-MINI-1U; MPN ESP32-S3-MINI-1U-N8; LCSC C2980299
U2: SN74LVC125APWR; TSSOP-14_4.4x5mm_P0.65mm; MPN SN74LVC125APWR; LCSC C7813

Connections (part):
+3V3: C1.1, C2.1, C3.1, C4.1, C6.1, C7.1, C8.1, J3.1, J3.3, J3.5, J3.7, J3.9, J3.11, J3.13, J3.15, J6.1, J6.3, J6.5, J6.7, J6.9, J6.11, J6.13, J6.15, J7.4 (VDD), R1.1, R2.1, R31.1, R32.1, R33.1, R34.1, R35.1, R36.1, TP1.1, U1.3 (3V3), U2.14 (VCC)
/A1V8: J3.42, J6.42
/AGND: J3.50, J6.50
/AREF: J3.48, J6.48
/AVN: J3.46, J6.46
/AVP: J3.44, J6.44
/BANKA_3: J1.3, J4.3
/BANKA_4: J1.4, J4.4
/BANKA_5: J1.5, J4.5
/BANKA_6: J1.6, J4.6
/BANKA_9: J1.9, J4.9
/BANKA_10: J1.10, J4.10
/BANKA_11: J1.11, J4.11
/BANKA_12: J1.12, J4.12
/BANKA_15: J1.15, J4.15
/BANKA_16: J1.16, J4.16
/BANKA_17: J1.17, J4.17
/BANKA_18: J1.18, J4.18
/BANKA_21: J1.21, J4.21
/BANKA_22: J1.22, J4.22
/BANKA_23: J1.23, J4.23
/BANKA_24: J1.24, J4.24
/BANKA_27: J1.27, J4.27
/BANKA_28: J1.28, J4.28
/BANKA_29: J1.29, J4.29
/BANKA_30: J1.30, J4.30
/BANKA_33: J1.33, J4.33
/BANKA_34: J1.34, J4.34
/BANKA_35: J1.35, J4.35
/BANKA_36: J1.36, J4.36
/BANKA_39: J1.39, J4.39
/BANKA_40: J1.40, J4.40
/BANKA_41: J1.41, J4.41
/BANKA_42: J1.42, J4.42
/BANKA_45: J1.45, J4.45
/BANKA_46: J1.46, J4.46
/BANKA_47: J1.47, J4.47
/BANKA_48: J1.48, J4.48
/BANKA_51: J1.51, J4.51
/BANKA_52: J1.52, J4.52
/BANKA_53: J1.53, J4.53
/BANKA_54: J1.54, J4.54
/BANKA_57: J1.57, J4.57
/BANKA_58: J1.58, J4.58
/BANKA_59: J1.59, J4.59
/BANKA_60: J1.60, J4.60
/BANKA_63: J1.63, J4.63
/BANKA_64: J1.64, J4.64
/BANKA_65: J1.65, J4.65
/BANKA_66: J1.66, J4.66
/BANKA_69: J1.69, J4.69
/BANKA_70: J1.70, J4.70
/BANKA_71: J1.71, J4.71
/BANKA_72: J1.72, J4.72
/BANKA_75: J1.75, J4.75
/BANKA_76: J1.76, J4.76
/BANKA_77: J1.77, J4.77
/BANKA_78: J1.78, J4.78
/BANKB_3: J2.3, J5.3
/BANKB_4: J2.4, J5.4
/BANKB_5: J2.5, J5.5
/BANKB_6: J2.6, J5.6
/BANKB_9: J2.9, J5.9
/BANKB_10: J2.10, J5.10
/BANKB_11: J2.11, J5.11
/BANKB_12: J2.12, J5.12
/BANKB_15: J2.15, J5.15
/BANKB_16: J2.16, J5.16
/BANKB_17: J2.17, J5.17
/BANKB_18: J2.18, J5.18
/BANKB_21: J2.21, J5.21
/BANKB_22: J2.22, J5.22
/BANKB_23: J2.23, J5.23
/BANKB_24: J2.24, J5.24
/BANKB_27: J2.27, J5.27
/BANKB_28: J2.28, J5.28
/BANKB_29: J2.29, J5.29
/BANKB_30: J2.30, J5.30
/BANKB_33: J2.33, J5.33
/BANKB_34: J2.34, J5.34
/BANKB_35: J2.35, J5.35
/BANKB_36: J2.36, J5.36
/BANKB_39: J2.39, J5.39
/BANKB_40: J2.40, J5.40
/BANKB_41: J2.41, J5.41
/BANKB_42: J2.42, J5.42
/BANKB_45: J2.45, J5.45
/BANKB_46: J2.46, J5.46
/BANKB_47: J2.47, J5.47
/BANKB_48: J2.48, J5.48
/BANKB_51: J2.51, J5.51
/BANKB_52: J2.52, J5.52
/BANKB_53: J2.53, J5.53
/BANKB_54: J2.54, J5.54
/BANKB_57: J2.57, J5.57
/BANKB_58: J2.58, J5.58
/BANKB_59: J2.59, J5.59
/BANKB_60: J2.60, J5.60
/BANKB_63: J2.63, J5.63
/BANKB_64: J2.64, J5.64
/BANKB_65: J2.65, J5.65
/BANKB_66: J2.66, J5.66
/BANKB_69: J2.69, J5.69
/BANKB_70: J2.70, J5.70
/BANKB_71: J2.71, J5.71
/BANKB_72: J2.72, J5.72
/BANKB_75: J2.75, J5.75
/BANKB_76: J2.76, J5.76
/BANKB_77: J2.77, J5.77
/BANKB_78: J2.78, J5.78
/ESP_BOOT: TP6.1, U1.4 (IO0)
/ESP_DONE: R6.2, U1.20 (IO16)
/ESP_EN: C5.1, R1.2, TP5.1, U1.45 (EN)
/ESP_FAB_CS: R23.1, U1.14 (IO10)
/ESP_FAB_IO2: R24.1, U1.18 (IO14)
/ESP_FAB_IO3: R25.1, U1.13 (IO9)
/ESP_FAB_IRQ: R26.1, U1.12 (IO8)
/ESP_FAB_MISO: R22.1, U1.17 (IO13)
/ESP_FAB_MOSI: R21.1, U1.15 (IO11)
/ESP_FAB_SCK: R20.1, U1.16 (IO12)
/ESP_FAB_SPARE: R27.1, U1.25 (IO21)
/ESP_RXD0: TP8.1, U1.40 (RXD0)
/ESP_TCK: U1.8 (IO4), U2.2
/ESP_TDI: U1.9 (IO5), U2.9
/ESP_TDO: R3.1, U1.10 (IO6), U2.11
/ESP_TMS: U1.11 (IO7), U2.5
/ESP_TXD0: TP7.1, U1.39 (TXD0)
/FAB_CS: J3.36, J6.36, R23.2
/FAB_IO2: J3.30, J6.30, R24.2
/FAB_IO3: J3.32, J6.32, R25.2
/FAB_IRQ: J3.33, J6.33, R26.2
/FAB_MISO: J3.34, J6.34, R22.2
/FAB_MOSI: J3.31, J6.31, R21.2
/FAB_SCK: J3.29, J6.29, R20.2
/FAB_SPARE: J3.35, J6.35, R27.2
/FPGA_DONE: J3.39, J6.39, R6.1
/FPGA_PROGRAM_B: J3.41, J6.41, Q1.3 (D)
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
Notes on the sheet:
Pt V2 Bank A -- pass-through J1 plug (bottom) <-> J4 receptacle (top) pin n <-> pin n, no connection to this card
Pt V2 Bank B -- pass-through J2 plug (bottom) <-> J5 receptacle (top) pin n <-> pin n, no connection to this card
Pt V2 J3 'Control' -- pass-through + taps JTAG pins 43/45/47/49 are REV DEPENDENT: nets J3_P43..J3_P49, strapped at R10-R17
U1 ESP32-S3-MINI-1U-N8: 8 MB flash, no PSRAM, external antenna connector. S3-MINI-1 shares the S2-MINI-1 land pattern (KiCad's S3 symbol uses the S2 footprint). GPIO3/45/46 are STRAPS, left floating on purpose. GPIO1/2/26/39-42 spare.
C1-C4 at U1 pin 3. R1/C5: EN RC delay, 10k/1uF per datasheet 9.
U2: JTAG buffer. R2 holds /OE HIGH, so the ESP32 is OFF the JTAG bus through its own boot and whenever firmware has not claimed it -- the Pt's USB/FT2232H path wins by default (README 4.2). R3 parks ESP_TDO while the buffer is off.
JTAG STRAPS -- populate R10-R13 for Pt V2 rev A (as built), OR R14-R17 for rev B. NEVER BOTH: that shorts two JTAG lines together. Rev B moves JTAG to the Au V2 order.
Q1/Q2 pull PROGRAM_B / Reset low only when the ESP32 drives the gate high. R4/R5 keep them OFF while GPIOs float at boot -- a bitstream is never lost to a reset glitch. R6: DONE is read-only; 1k limits current if the GPIO is ever misconfigured as output.
ESP32 <-> fabric SPI on J3 29-36 (README 3b). SCK/MOSI/MISO/CS/IO2/IO3 on the S3's IO_MUX FSPI pins, so quad SPI at 80 MHz is available without the GPIO matrix. Banks 14 and 34 are 3.3 V (bank 13 is the only 2.5 V bank) -- confirm VCCO before first use.
J7 microSD, 1.42 mm tall -- TOP face only (SD_BITSTREAM_LIBRARY 3). 10k pull-ups on CMD/DAT0-3 per the SD spec. Detect switch 9-10 -> SD_CD_N.
Pad field for first flash / recovery -- place at the enclosure's open face. USB_DP/DN = GPIO20/19 (native USB-Serial-JTAG). ESP_BOOT = GPIO0: hold low + pulse EN. TP1-TP8 are bare copper: no part, not in the BOM or CPL.
LauEsp32Config_Pt_Stack -- ESP32 wireless programmer, Pt V2 element card. GENERATED by gen_schematic.py -- edit the script, not this sheet. Design notes: SCHEMATIC.md. Every assembled part carries an LCSC code; check_jlc_parts.py verifies code, MPN and stock.

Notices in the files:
README.md:
Licensing:
The HDMI pass-through foundation is adapted from
